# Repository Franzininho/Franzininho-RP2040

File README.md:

# Franzininho-RP2040

Placa para teste do RP2040

## Brainstorming

### Recursos:
- Display IPS com st7735 [1.3 TFT](https://pt.aliexpress.com/item/4001282467099.html?spm=a2g0o.productlist.0.0.2600479fzkLFuy&algo_pvid=41604a7a-2572-4824-af54-ab23fa447bef&algo_exp_id=41604a7a-2572-4824-af54-ab23fa447bef-2&pdp_ext_f=%7B%22sku_id%22%3A%2212000017591977476%22%7D&pdp_pi=-1%3B15.47%3B-1%3B-1%40salePrice%3BBRL%3Bsearch-mainSearch)
- Formato conoforme esse guia (https://github.com/microsoft/pxt-arcade-hardware-designs/pulls)
- Conector para micro sd card [exemplo](https://pt.aliexpress.com/item/1005002327556213.html?spm=a2g0o.productlist.0.0.5e17d13bajhceq&algo_pvid=1e473f28-a7a4-45c7-b086-8bc26ea62537&algo_exp_id=1e473f28-a7a4-45c7-b086-8bc26ea62537-2&pdp_ext_f=%7B%22sku_id%22%3A%2212000020103778220%22%7D&pdp_pi=-1%3B1.66%3B-1%3B2221%40salePrice%3BBRL%3Bsearch-mainSearch)
- Bateria - Circuito para gerenciamento de carga
- Pinout para hc-05 (UART)
- USB: Micro
- USB HOST usando PIO 
    https://youtu.be/2eB8p8vo7lw
    https://github.com/pa-art/test_usb_host
    https://github.com/sekigon-gonnoc/qmk_firmware/tree/rp2040/keyboards/pico_pico_usb
- Saída de áudio
- Saída video 
- Expansões: i²c, spi   
 - OPÇÃO:
    - Fazer teclado como placa de expansão
    - Comunicação infrared: https://youtu.be/LPeMlFf0Qso  https://youtu.be/GHWm4mRImoI
    - Motor vibracall
 
### Referências

RP2040:
- https://arcade.makecode.com/hardware/adding
- https://github.com/microsoft/pxt-arcade-hardware-designs/tree/master/ArcadeMVD-STM%20v1.5
- https://news.mkme.org/?p=21518
- https://github.com/microsoft/pxt-arcade-hardware-designs/tree/master/microbit-shield
- https://datasheets.raspberrypi.com/pico/pico-datasheet.pdf
- https://www.sparkfun.com/rp2040#resources
- https://www.youtube.com/watch?v=2eB8p8vo7lw
- https://github.com/pa-art/test_usb_host
- https://github.com/sekigon-gonnoc/qmk_firmware/tree/rp2040/keyboards/pico_pico_usb
- https://learn.adafruit.com/adafruit-pygamer/which-board
- https://www.cnx-software.com/2021/12/31/mico-a-usb-microphone-based-on-raspberry-pi-rp2040-mcu/

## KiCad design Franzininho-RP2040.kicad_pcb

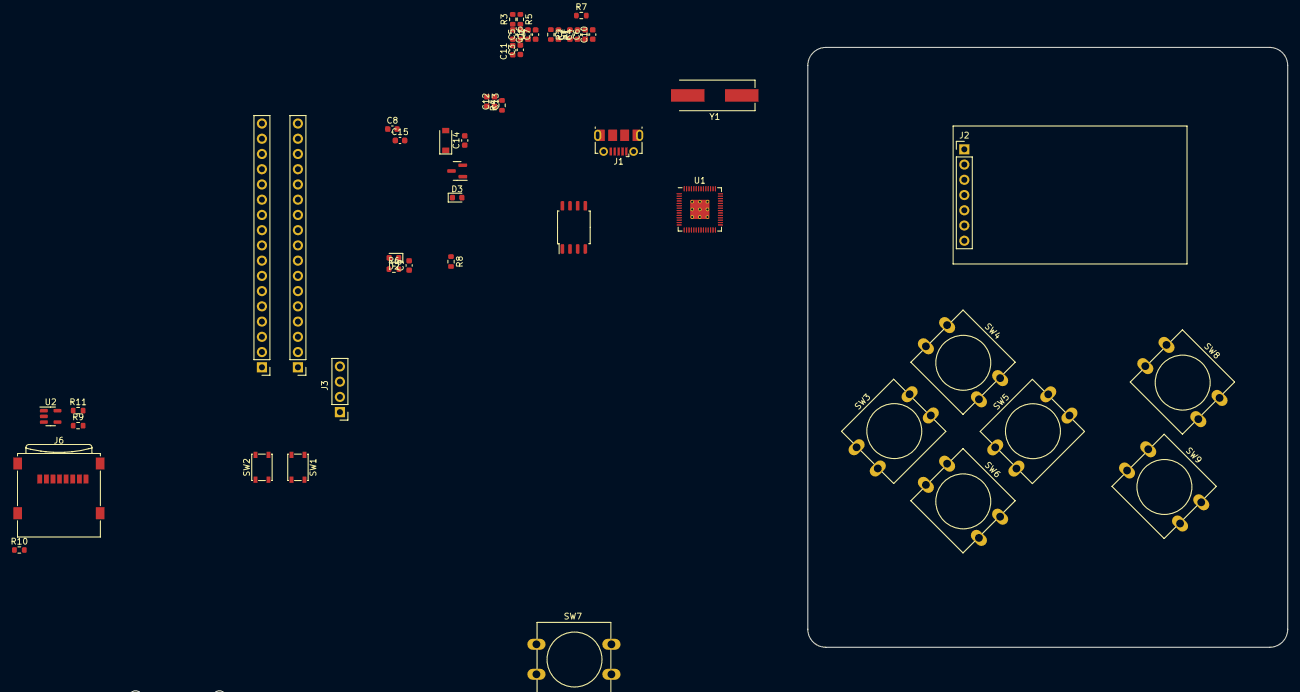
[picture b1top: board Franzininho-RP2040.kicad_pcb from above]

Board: 2 copper layers, 80.0 x 100.0 mm, 54 parts (0 on the bottom side), 55 nets, no tracks yet.

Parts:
C1, C3: 1u; C_0603_1608Metric
C2, C4, C5, C6, C7, C8, C9, C10, C11, C16: 100n; C_0603_1608Metric
C12, C13: 27p; C_0603_1608Metric
C14, C15: 10u; C_0603_1608Metric
D1: 1N5819W; D_SOD-123
D2, D3: LED; LED_0603_1608Metric
H1, H2, H3, H4: MountingHole; MountingHole_2.2mm_M2
J1: USB_B_Micro; USB_Micro-B_Molex-105017-0001
J2: Conn_01x07_Male; PinHeader_1x07_P2.54mm_Vertical
J3: Conn_01x04; PinHeader_1x04_P2.54mm_Vertical
J4, J5: Conn_01x17; PinHeader_1x17_P2.54mm_Vertical
J6: Micro_SD_Card; microSD_HC_Wuerth_693072010801
R1, R2: 27; R_0603_1608Metric
R3, R4: 1k; R_0603_1608Metric
R5, R6, R7, R8, R10: 10k; R_0603_1608Metric
R9: 100k; R_0603_1608Metric
R11: DNF; R_0603_1608Metric
SW1, SW2: SW_Push; SW_SPST_PTS810
SW3, SW4, SW5, SW6, SW7, SW8, SW9: SW_Push; SW_PUSH-12mm
U1: RP2040; RP2040-QFN-56
U2: XC6206P332MR; SOT-23
U2#2: AP2112K-3.3; SOT-23-5
U3: W25Q128JVS; SOIC-8_5.23x5.23mm_P1.27mm
Y1: 12MHz; Crystal_SMD_HC49-US

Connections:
+1V1: C3.1, C5.1, C7.1, U1.23 (DVDD), U1.45 (VREG_VOUT), U1.50 (DVDD1)
+3V3: C1.1, C2.1, C4.1, C6.1, C8.1, C9.1, C10.1, C11.1, C15.1, C16.1, J3.1, J4.1, J6.4 (VDD), R5.2, R6.2, R8.2, R10.1, U1.1 (IOVDD), U1.10 (IOVDD1), U1.22 (IOVDD2), U1.33 (IOVDD3), U1.42 (IOVDD4), U1.43 (ADC_AVDD), U1.44 (VREG_VIN), U1.48 (USB_VDD), U1.49 (IOVDD5), U2.2 (VO), U2#2.5 (VOUT), U3.8 (VCC)
+5V: D1.1 (K), J5.1, R9.1, U2.3 (VI), U2#2.1 (VIN)
/BT_A: SW5.1, U1.16 (GPIO13)
/BT_B: SW4.1, U1.17 (GPIO14)
/BT_DOWN: SW6.1, U1.15 (GPIO12)
/BT_LEFT: SW9.1, U1.12 (GPIO9)
/BT_MENU: SW3.1, U1.18 (GPIO15)
/BT_RIGHT: SW8.1, U1.13 (GPIO10)
/BT_UP: SW7.1, U1.14 (GPIO11)
/DISPLAY_DC: J2.6, U1.6 (GPIO4)
/DISPLAY_RES: J2.5, U1.7 (GPIO5)
/DISPLAY_SCL: J2.3, U1.4 (GPIO2)
/DISPLAY_SDA: J2.4, U1.5 (GPIO3)
/GPIO0: J4.17, U1.2 (GPIO0)
/GPIO6: J4.11, U1.8 (GPIO6)
/GPIO7: J4.10, U1.9 (GPIO7)
/GPIO8: J4.9, U1.11 (GPIO8)
/GPIO16: J5.5, U1.27 (GPIO16)
/GPIO17: J5.6, U1.28 (GPIO17)
/GPIO19: J5.8, U1.30 (GPIO19)
/GPIO23: J5.12, U1.35 (GPIO23)
/GPIO24: J5.13, U1.36 (GPIO24)
/GPIO25: R7.2, U1.37 (GPIO25)
/GPIO26_ADC0: J5.14, U1.38 (GPIO26/ADC0)
/GPIO27_ADC1: J5.15, U1.39 (GPIO27/ADC1)
/GPIO28_ADC2: J5.16, U1.40 (GPIO28/ADC2)
/GPIO29_ADC3: J5.17, U1.41 (GPIO29/ADC3)
/POWER_LED: D2.2 (A), R6.1
/QSPI_CLK: U1.52 (QSPI_SCLK), U3.6 (CLK)
/QSPI_SD0: U1.53 (QSPI_SD0), U3.5 (DI(IO0))
/QSPI_SD1: U1.55 (QSPI_SD1), U3.2 (DO(IO1))
/QSPI_SD2: U1.54 (QSPI_SD2), U3.3 (IO2)
/QSPI_SD3: U1.51 (QSPI_SD3), U3.7 (IO3)
/QSPI_SS: R3.1, R5.1, U1.56 (QSPI_SS_N), U3.1 (~CS)
/SD_CLK: J6.5 (CLK), R11.1, U1.3 (GPIO1)
/SD_CMD: J6.3 (CMD), U1.29 (GPIO18)
/SD_DAT1: J6.8 (DAT1), U1.31 (GPIO20)
/SD_DAT2: J6.1 (DAT2), R10.2, U1.32 (GPIO21)
/SD_DAT3: J6.2 (DAT3/CD), U1.34 (GPIO22)
/SWCLK: J3.2, U1.24 (SWCLK)
/SWDIO: J3.3, U1.25 (SWDIO)
/USB_D+: J1.3 (D+), R2.1
/USB_D-: J1.2 (D-), R1.1
/USER_LED: D3.2 (A), R7.1
/XIN: C12.1, U1.20 (XIN), Y1.1
/XOUT: R4.1, U1.21 (XOUT)
/XOUT_R: C13.1, R4.2, Y1.2
/~RESET: R8.1, SW2.2, U1.26 (RUN)
/~USB_BOOT: R3.2, SW1.2
GND: C1.2, C2.2, C3.2, C4.2, C5.2, C6.2, C7.2, C8.2, C9.2, C10.2, C11.2, C12.2, C13.2, C14.2, C15.2, C16.2, D2.1 (K), D3.1 (K), J1.5 (GND), J1.6 (Shield), J2.1, J3.4, J4.2, J5.2, J5.3, J6.6 (VSS), J6.9 (SHIELD), R11.2, SW1.1, SW2.1, SW3.2, SW4.2, SW5.2, SW6.2, SW7.2, SW8.2, SW9.2, U1.19 (TESTEN), U1.57 (PAD), U2.1 (GND), U2#2.2 (GND), U3.4 (GND)
unnamed: R1.2, U1.46 (USB_DM)
unnamed: R2.2, U1.47 (USB_DP)
unnamed: R9.2, U2#2.3 (EN)
VBUS: C14.1, D1.2 (A), J1.1 (VBUS)

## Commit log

2021-09-25 Adicionando Readme
2021-09-25 Circuito base inicial
2021-11-27 Adição de conector SWD, definição de pinos e pequenas correções
2021-12-19 Anotação de esquemático
2021-12-19 ERC e correções
2021-12-22 Adição de nomes de nets + pequenas melhorias e correções
2021-12-22 Geração de netlist e posicionamento inicial de componentes na PCB
2021-12-29 Adição de modelos 3D e melhorias
2022-01-30 Atualização para KiCad 6
2022-01-30 Adição de título
2022-02-03 Pequena melhoria nos textos do esquemático
2022-02-04 Incluindo brainstoming para recursos
2022-02-04 Incluindo exemplo
2022-02-04 Mais ideias
2022-02-04 Ajuste de bullet points
2022-02-04 Mais opções de recursos
2022-02-04 Incluindo mais recursos
2022-02-10 Aumentar layout da página de esquemático
2022-03-01 Adição de display, botões e cartão SD
2022-03-11 Atualização da PCB
2022-03-12 Ajuste do outline da placa
